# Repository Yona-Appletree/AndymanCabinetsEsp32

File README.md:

# Cabinet Controller

## IP Addresses
North Pixlite: 192.168.8.20
South Pixlite: 192.168.8.21

Router: 192.168.8.1
South Bridge: 192.168.8.138

## Prerequisties

    brew install platformio

## USB

Upload & Monitor:

    pio run -e usb -t upload -t monitor
    
Monitor:

    pio run -e usb -t monitor
    
## OTA

PlatformIO OTA Info: https://docs.platformio.org/en/latest/platforms/espressif32.html#over-the-air-ota-update

Upload:

    pio run -e ota -t upload
    
Upload and Monitor (with USB connected):

    pio run -e ota -t upload && pio run -e usb -t monitor

## Notes

PlatformIO Documentation: https://docs.platformio.org/en/latest/quickstart.html

Install Library: pio lib install "FastLED"
wESP Documentation: https://wesp32.com/software/

## TODO

- [ ] Refactor programs into class
- [ ] Support preview of programs
- [ ] Indicate selector positions

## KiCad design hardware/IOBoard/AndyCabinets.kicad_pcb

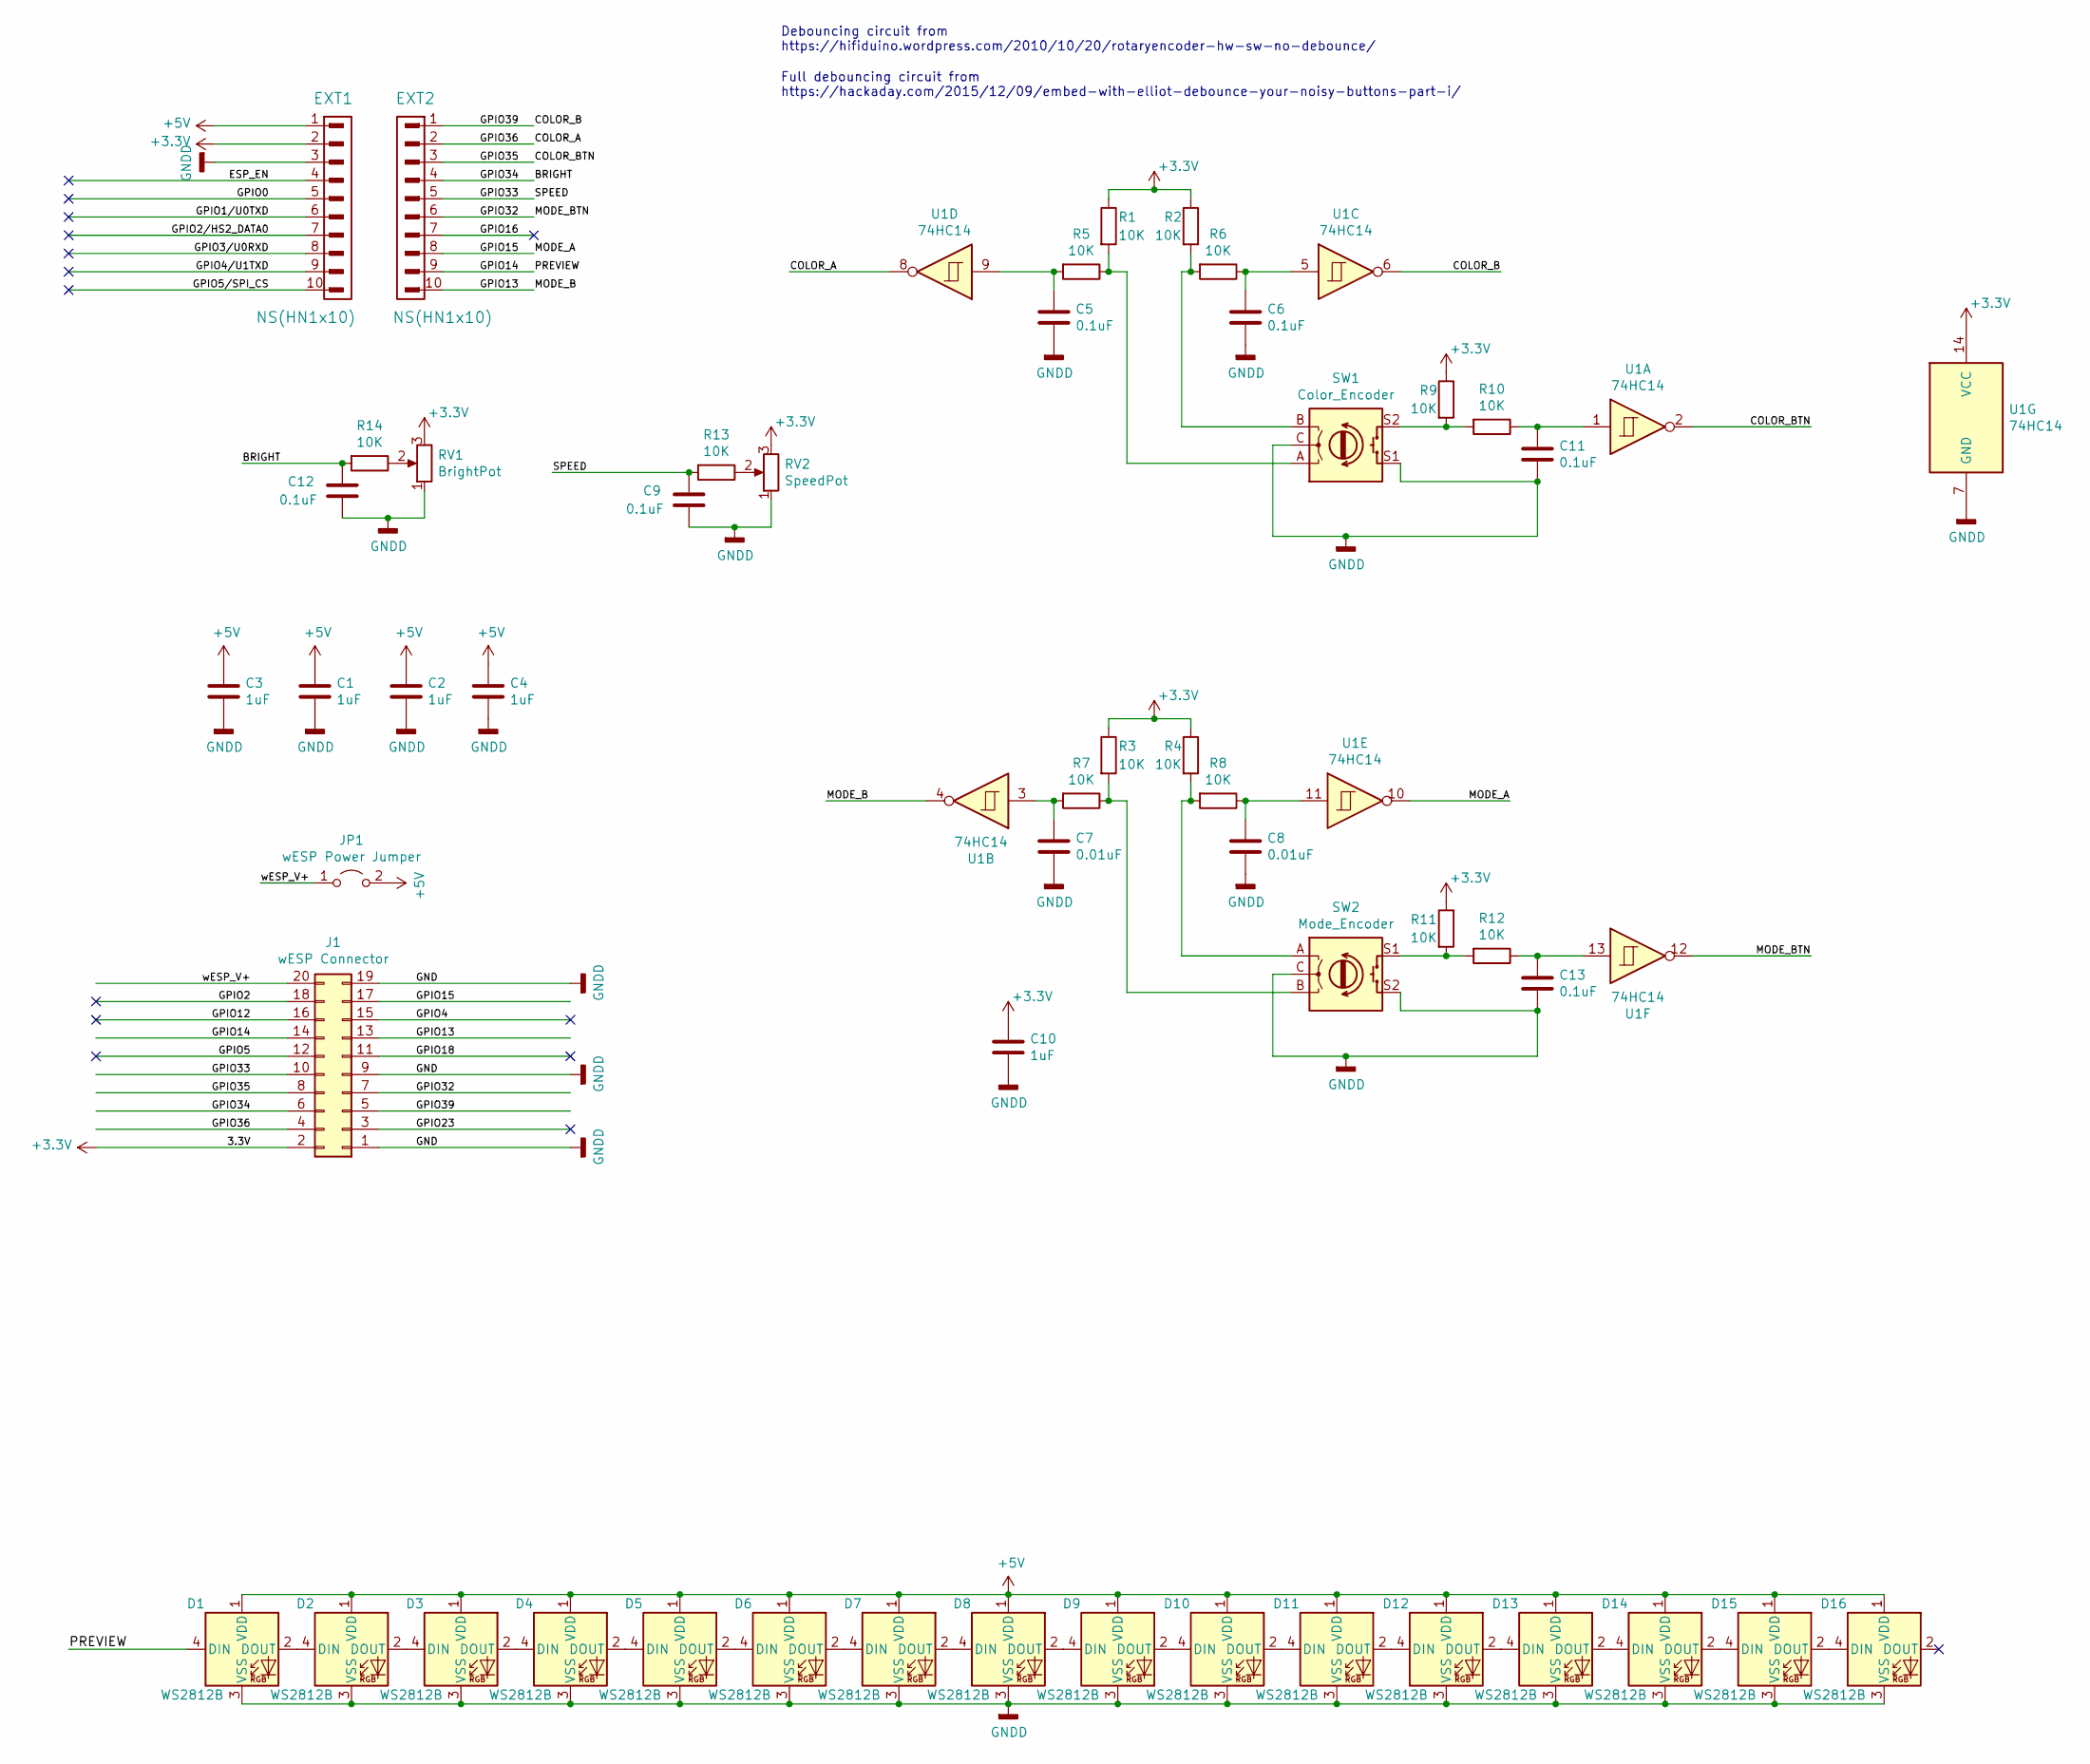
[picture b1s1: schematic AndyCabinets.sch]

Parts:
C1, C2, C3, C4, C10: 1uF; C_0805_2012Metric
C5, C6, C9, C11, C12, C13: 0.1uF; C_0402_1005Metric
C7, C8: 0.01uF; C_0402_1005Metric
D1, D2, D3, D4, D5, D6, D7, D8, D9, D10, D11, D12, D13, D14, D15, D16: WS2812B; LED_SK6812MINI_PLCC4_3.5x3.5mm_P1.75mm
EXT1, EXT2: NS(HN1x10); PinHeader_1x10_P2.54mm_Vertical_SMD_Pin1Left
J1: wESP Connector; PinSocket_2x10_P2.54mm_Vertical_SMD_Mirror
JP1: wESP Power Jumper; SolderJumper-2_P1.3mm_Open_TrianglePad1.0x1.5mm
R1, R2, R3, R4, R5, R6, R7, R8, R9, R10, R11, R12, R13, R14: 10K; R_0402_1005Metric
RV1: BrightPot; Potentiometer_TT_P0915N_Flush
RV2: SpeedPot; Potentiometer_TT_P0915N_Flush
SW1: Color_Encoder; RotaryEncoder_Alps_EC12E-SMDSwitch_Vertical_H20mm_CircularM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
SW2: Mode_Encoder; RotaryEncoder_Alps_EC12E-Switch_Vertical_H20mm_CircularMoun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
U1: 74HC14; SOIC-14_3.9x8.7mm_P1.27mm

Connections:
+3V3: C10.1, EXT1.2, J1.2, R1.1, R2.1, R3.1, R4.1, R9.1, R11.1, RV1.3, RV2.3, U1.14 (VCC)
+5V: C1.1, C2.1, C3.1, C4.1, D1.1 (VDD), D2.1 (VDD), D3.1 (VDD), D4.1 (VDD), D5.1 (VDD), D6.1 (VDD), D7.1 (VDD), D8.1 (VDD), D9.1 (VDD), D10.1 (VDD), D11.1 (VDD), D12.1 (VDD), D13.1 (VDD), D14.1 (VDD), D15.1 (VDD), D16.1 (VDD), EXT1.1, JP1.2 (B)
/BRIGHT: C12.1, EXT2.4, J1.6, R14.2
/COLOR_A: EXT2.2, J1.4, U1.8
/COLOR_B: EXT2.1, J1.5, U1.6
/COLOR_BTN: EXT2.3, J1.8, U1.2
/ESP_EN: EXT1.4
/GPIO0: EXT1.5
/GPIO1/U0TXD: EXT1.6
/GPIO2: J1.18
/GPIO2/HS2_DATA0: EXT1.7
/GPIO3/U0RXD: EXT1.8
/GPIO4: J1.15
/GPIO4/U1TXD: EXT1.9
/GPIO5: J1.12
/GPIO5/SPI_CS: EXT1.10
/GPIO12: J1.16
/GPIO13: EXT2.10, J1.13, U1.4
/GPIO14: D1.4 (DIN), EXT2.9, J1.14
/GPIO15: EXT2.8, J1.17, U1.10
/GPIO16: EXT2.7
/GPIO18: J1.11
/GPIO23: J1.3
/GPIO32: EXT2.6, J1.7, U1.12
/GPIO33: C9.1, EXT2.5, J1.10, R13.2
/wESP_V+: J1.20, JP1.1 (A)
GNDD: C1.2, C2.2, C3.2, C4.2, C5.2, C6.2, C7.2, C8.2, C9.2, C10.2, C11.2, C12.2, C13.2, D1.3 (VSS), D2.3 (VSS), D3.3 (VSS), D4.3 (VSS), D5.3 (VSS), D6.3 (VSS), D7.3 (VSS), D8.3 (VSS), D9.3 (VSS), D10.3 (VSS), D11.3 (VSS), D12.3 (VSS), D13.3 (VSS), D14.3 (VSS), D15.3 (VSS), D16.3 (VSS), EXT1.3, J1.1, J1.9, J1.19, RV1.1, RV2.1, SW1.C, SW1.S1, SW2.C, SW2.S2, U1.7 (GND)
unnamed: C5.1, R5.2, U1.9
unnamed: C6.1, R6.1, U1.5
unnamed: C7.1, R7.2, U1.3
unnamed: C8.1, R8.1, U1.11
unnamed: C11.1, R10.1, U1.1
unnamed: C13.1, R12.1, U1.13
unnamed: D1.2 (DOUT), D2.4 (DIN)
unnamed: D2.2 (DOUT), D3.4 (DIN)
unnamed: D3.2 (DOUT), D4.4 (DIN)
unnamed: D4.2 (DOUT), D5.4 (DIN)
unnamed: D5.2 (DOUT), D6.4 (DIN)
unnamed: D6.2 (DOUT), D7.4 (DIN)
unnamed: D7.2 (DOUT), D8.4 (DIN)
unnamed: D8.2 (DOUT), D9.4 (DIN)
unnamed: D10.2 (DOUT), D11.4 (DIN)
unnamed: D9.2 (DOUT), D10.4 (DIN)
unnamed: D11.2 (DOUT), D12.4 (DIN)
unnamed: D12.2 (DOUT), D13.4 (DIN)
unnamed: D13.2 (DOUT), D14.4 (DIN)
unnamed: D14.2 (DOUT), D15.4 (DIN)
unnamed: D15.2 (DOUT), D16.4 (DIN)
unnamed: R1.2, R5.1, SW1.A
unnamed: R2.2, R6.2, SW1.B
unnamed: R3.2, R7.1, SW2.B
unnamed: R4.2, R8.2, SW2.A
unnamed: R9.2, R10.2, SW1.S2
unnamed: R11.2, R12.2, SW2.S1
unnamed: R13.1, RV2.2
unnamed: R14.1, RV1.2

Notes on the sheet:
Debouncing circuit from https://hifiduino.wordpress.com/2010/10/20/rotaryencoder-hw-sw-no-debounce/
Full debouncing circuit from https://hackaday.com/2015/12/09/embed-with-elliot-debounce-your-noisy-buttons-part-i/

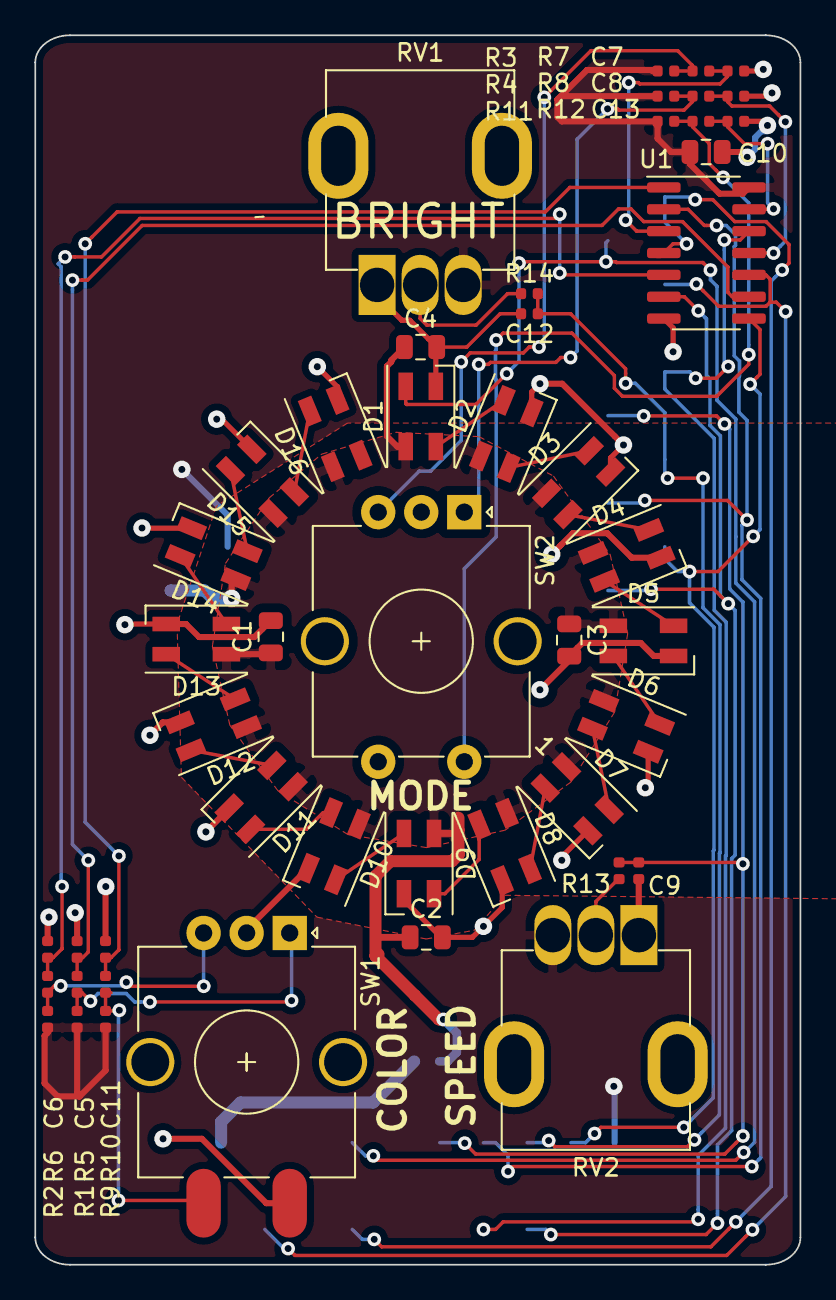
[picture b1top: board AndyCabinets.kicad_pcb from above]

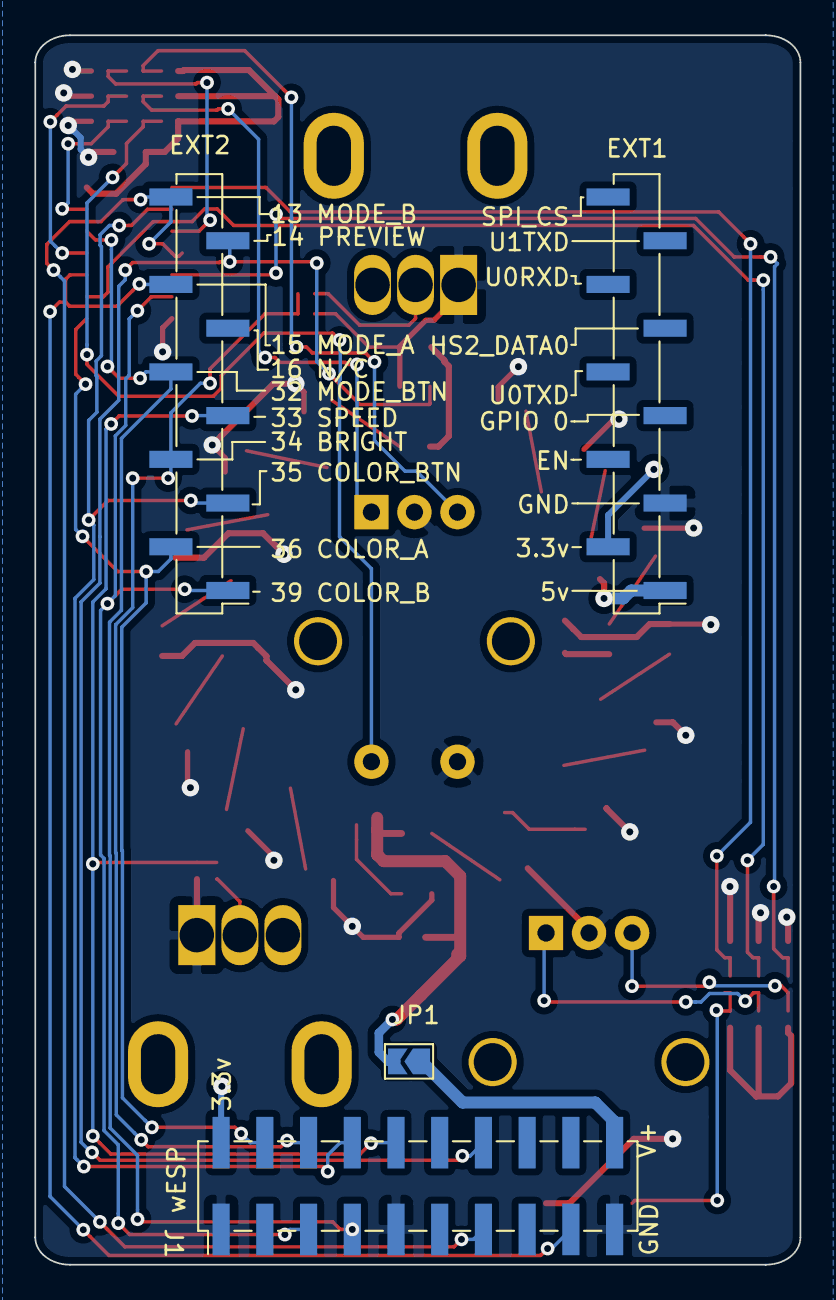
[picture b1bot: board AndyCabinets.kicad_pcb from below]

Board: 2 copper layers, 44.4 x 71.4 mm, 52 parts (4 on the bottom side), 42 nets.

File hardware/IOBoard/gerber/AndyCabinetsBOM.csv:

"Id";"Designator";"Package";"Quantity";"Designation";"Supplier and ref";
1;"SW1";"RotaryEncoder_Alps_EC12E-SMDSwitch_Vertical_H20mm_CircularMountingHoles";1;"Color_Encoder";;;
2;"J1";"PinSocket_2x10_P2.54mm_Vertical_SMD_Mirror";1;"wESP Connector";;;
3;"JP1";"SolderJumper-2_P1.3mm_Open_TrianglePad1.0x1.5mm";1;"wESP Power Jumper";;;
4;"EXT2,EXT1";"PinHeader_1x10_P2.54mm_Vertical_SMD_Pin1Left";2;"NS(HN1x10)";;;
5;"D2,D16,D15,D1,D14,D13,D12,D11,D10,D9,D8,D7,D6,D5,D4,D3";"LED_SK6812MINI_PLCC4_3.5x3.5mm_P1.75mm";16;"WS2812B";;;
6;"R14,R13,R12,R11,R10,R9,R8,R7,R6,R5,R4,R3,R2,R1";"R_0402_1005Metric";14;"10K";;;
7;"C12,C9,C13,C11,C6,C5";"C_0402_1005Metric";6;"0.1uF";;;
8;"C10,C4,C3,C2,C1";"C_0805_2012Metric";5;"1uF";;;
9;"RV2";"Potentiometer_TT_P0915N_Flush";1;"SpeedPot";;;
10;"RV1";"Potentiometer_TT_P0915N_Flush";1;"BrightPot";;;
11;"U1";"SOIC-14_3.9x8.7mm_P1.27mm";1;"74HC14";;;
12;"C8,C7";"C_0402_1005Metric";2;"0.01uF";;;
13;"SW2";"RotaryEncoder_Alps_EC12E-Switch_Vertical_H20mm_CircularMountingHoles";1;"Mode_Encoder";;;

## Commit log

2019-12-31 Updated notes, added hardware
2019-12-31 README
2020-01-01 Initial blind implementation of renderers
2020-01-01 Added cmake builds to .gitignore
2020-01-01 Added idea project
2020-01-01 Removed commented block
2020-01-02 Updated schematic to use 3.3v for analog inputs
2020-01-02 First basic working test
2020-01-02 Minor schematic cleanup
2020-01-02 Better color handling, multi-core use
2020-01-02 Hardware: Rotary Encoder Play
2020-01-05 Rotary Encoder Board Work
2020-01-05 Added faceplate boards
2020-01-05 Pre-larger inside board relayout
2020-01-16 After PCB v2
2020-01-22 Initial working remote version; some minor PCB changes
2020-01-23 Rev 3 PCB
2020-01-24 Refactored visualizations and improved preview; Moved networking to main core; Wifi support added but disabled on current hardware;
2020-01-24 Hardware v3-beta1 (not run yet)
2020-01-24 Fixed typo
2020-01-24 Added new pulse visualization
2020-01-24 Added visualization effects
2020-01-25 Added dial indicators v1
2020-01-25 Many UI improvements; better rainbow palette; various other minor tweaks
2020-01-25 More UI improvements, reverted speed changes due to jitter
2020-01-25 Minor color improvements
2020-01-25 Minor cleanup to fps handling
2021-06-02 Changes from install at Andy's house
2021-06-02 More changes from andy's
2021-06-02 Hardware pre change to SMD2020
